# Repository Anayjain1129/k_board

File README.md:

# K-Board

# Features:

- Rotary Encoder for volume control
- Raspberry Pi Pico
- Customised layout
- QMK firmware
- Awesome Case

# Schematics

# PCB

# Case

# 3d View of all parts together

# BOM
| Name | Quantity | Cost | Link |
|------|----------|------|------|
| TTC Silent Red V3 | 84 | $45.11 | [Buy](https://stackskb.com/store/ttc-silent-red-v3-switch/) |
| Durock Smokey Screw-In Stabilizers V2 (4+1 w/ 6.25u spacebar) | 1 | $17.01 | [Buy](https://stackskb.com/store/durock-smokey-screw-in-stabilizers-v2/) |
| EC11 Rotary Encoder with Switch | 1 | $0.00 | Self-sourced |
| Mount Fuji Premium Moa Profile PBT Keycap | 1 | $28.78 | [Buy](https://curiositycaps.in/products/fugaju-premium-moa-profile-pbt-keycap?_pos=21&_sid=c0043ab41&_ss=r) |
| Diode 1N4148 Through-Hole | 100 | $1.06 | [Buy](https://www.amazon.in/dp/B084ZP5BJ3) |
| PCB - (Black Color) | 5 | $40.00 | [Buy](https://jlcpcb.com/) |
| Raspberry Pi Pico | 1 | $6.40 | [Buy](https://www.amazon.in/Raspberry-Pi-Headers-Soldered-Micro/dp/B08WPNM7JB) |
| Heatset and Screws | 1 | $0.00 | Self-sourced |
| Case (top, mid, bot) | 1 | $0.00 | Self-sourced |
| **Total** | | **$138.36** | |

The price may fluctuate due to dollar market trend

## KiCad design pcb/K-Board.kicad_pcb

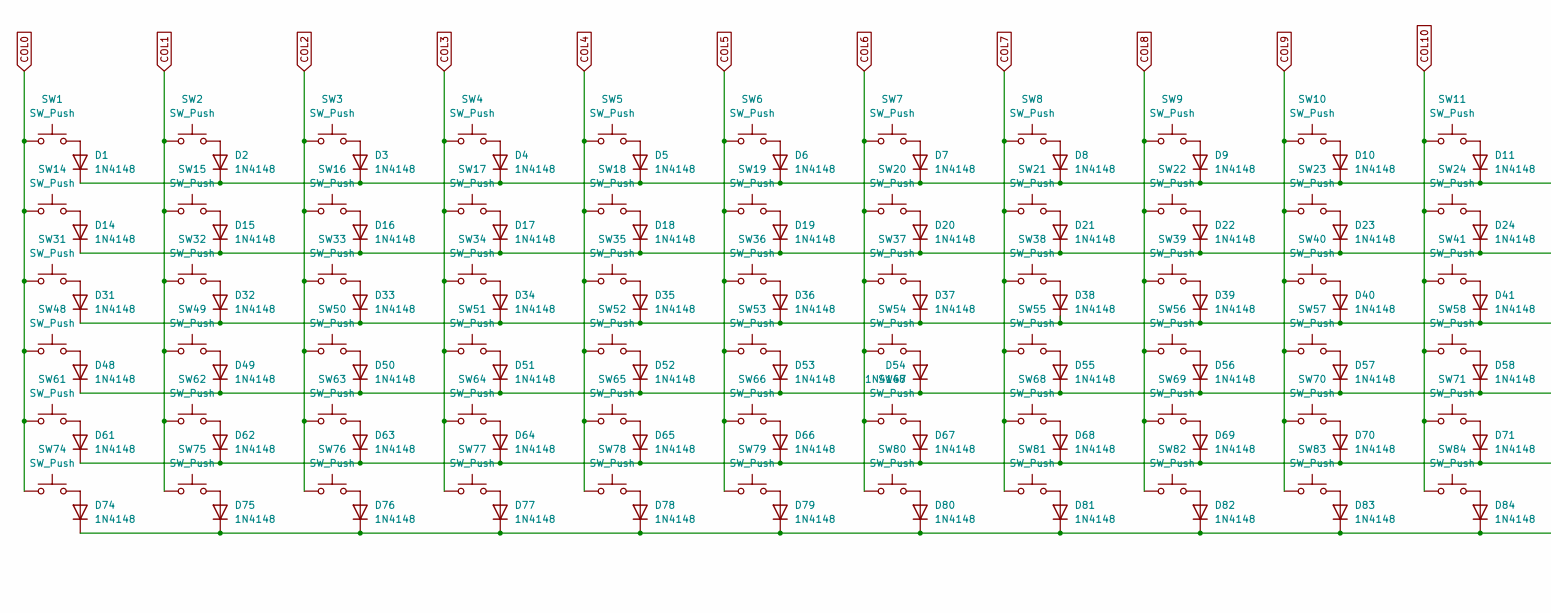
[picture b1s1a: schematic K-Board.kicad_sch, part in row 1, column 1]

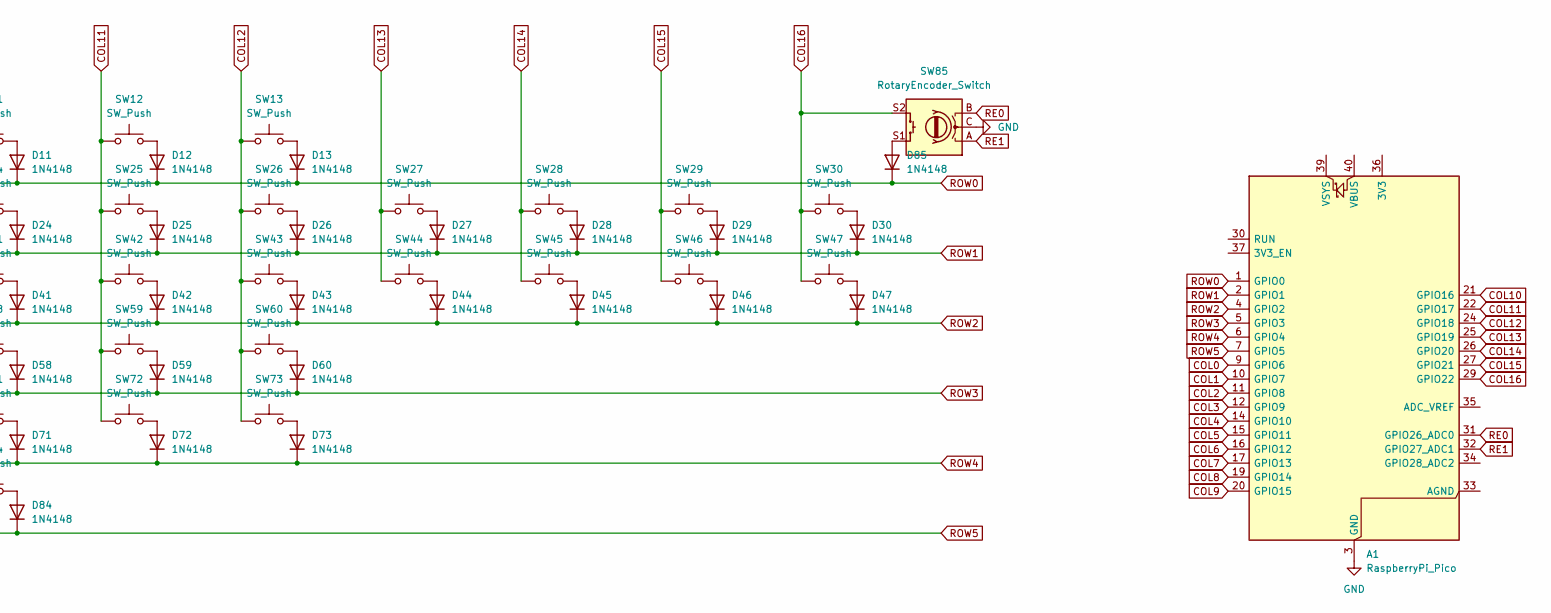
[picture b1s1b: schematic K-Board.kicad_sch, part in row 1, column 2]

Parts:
A1: RaspberryPi_Pico; RaspberryPi_Pico_Common_Unspecified
D1, D2, D3, D4, D5, D6, D7, D8, D9, D10, D11, D12, D13, D14, D15, D16, D17, D18, D19, D20, D21, D22, D23, D24, D25, D26, D27, D28, D29, D30, D31, D32, D33, D34, D35, D36, D37, D38, D39, D40, D41, D42, D43, D44, D45, D46, D47, D48, D49, D50, D51, D52, D53, D54, D55, D56, D57, D58, D59, D60, D61, D62, D63, D64, D65, D66, D67, D68, D69, D70, D71, D72, D73, D74, D75, D76, D77, D78, D79, D80, D81, D82, D83, D84, D85: 1N4148; D_DO-35_SOD27_P7.62mm_Horizontal
SW1, SW2, SW3, SW4, SW5, SW6, SW7, SW8, SW9, SW10, SW11, SW12, SW13, SW14, SW15, SW16, SW17, SW18, SW19, SW20, SW21, SW22, SW23, SW24, SW25, SW26, SW27, SW28, SW29, SW31, SW33, SW34, SW35, SW36, SW37, SW38, SW39, SW40, SW41, SW42, SW43, SW44, SW46, SW48, SW49, SW50, SW51, SW52, SW53, SW54, SW55, SW56, SW57, SW58, SW60, SW62, SW63, SW64, SW65, SW66, SW67, SW68, SW69, SW70, SW71, SW73, SW74, SW79, SW80, SW81, SW82, SW83, SW84: SW_Push; SW_Cherry_MX_1.00u_PCB
SW30: SW_Push; SW_Cherry_MX_2.00u_PCB
SW32, SW45: SW_Push; SW_Cherry_MX_1.50u_PCB
SW47, SW72: SW_Push; SW_Cherry_MX_1.75u_PCB
SW59, SW61: SW_Push; SW_Cherry_MX_2.25u_PCB
SW75, SW76, SW77: SW_Push; SW_Cherry_MX_1.25u_PCB
SW78: SW_Push; SW_Cherry_MX_6.25u_PCB
SW85: RotaryEncoder_Switch; RotaryEncoder_Alps_EC12E-Switch_Vertical_H20mm_CircularMoun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

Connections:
COL0: A1.9 (GPIO6), SW1.1, SW14.1, SW31.1, SW48.1, SW61.1, SW74.1
COL1: A1.10 (GPIO7), SW2.1, SW15.1, SW32.1, SW49.1, SW62.1, SW75.1
COL2: A1.11 (GPIO8), SW3.1, SW16.1, SW33.1, SW50.1, SW63.1, SW76.1
COL3: A1.12 (GPIO9), SW4.1, SW17.1, SW34.1, SW51.1, SW64.1, SW77.1
COL4: A1.14 (GPIO10), SW5.1, SW18.1, SW35.1, SW52.1, SW65.1, SW78.1
COL5: A1.15 (GPIO11), SW6.1, SW19.1, SW36.1, SW53.1, SW66.1, SW79.1
COL6: A1.16 (GPIO12), SW7.1, SW20.1, SW37.1, SW54.1, SW67.1, SW80.1
COL7: A1.17 (GPIO13), SW8.1, SW21.1, SW38.1, SW55.1, SW68.1, SW81.1
COL8: A1.19 (GPIO14), SW9.1, SW22.1, SW39.1, SW56.1, SW69.1, SW82.1
COL9: A1.20 (GPIO15), SW10.1, SW23.1, SW40.1, SW57.1, SW70.1, SW83.1
COL10: A1.21 (GPIO16), SW11.1, SW24.1, SW41.1, SW58.1, SW71.1, SW84.1
COL11: A1.22 (GPIO17), SW12.1, SW25.1, SW42.1, SW59.1, SW72.1
COL12: A1.24 (GPIO18), SW13.1, SW26.1, SW43.1, SW60.1, SW73.1
COL13: A1.25 (GPIO19), SW27.1, SW44.1
COL14: A1.26 (GPIO20), SW28.1, SW45.1
COL15: A1.27 (GPIO21), SW29.1, SW46.1
COL16: A1.29 (GPIO22), SW30.1, SW47.1, SW85.S2
GND: A1.3 (GND), A1.8 (GND), A1.13 (GND), A1.18 (GND), A1.23 (GND), A1.28 (GND), A1.38 (GND), SW85.C
unnamed: D1.2 (A), SW1.2
unnamed: D2.2 (A), SW2.2
unnamed: D3.2 (A), SW3.2
unnamed: D4.2 (A), SW4.2
unnamed: D5.2 (A), SW5.2
unnamed: D6.2 (A), SW6.2
unnamed: D7.2 (A), SW7.2
unnamed: D8.2 (A), SW8.2
unnamed: D9.2 (A), SW9.2
unnamed: D10.2 (A), SW10.2
unnamed: D11.2 (A), SW11.2
unnamed: D12.2 (A), SW12.2
unnamed: D13.2 (A), SW13.2
unnamed: D14.2 (A), SW14.2
unnamed: D15.2 (A), SW15.2
unnamed: D16.2 (A), SW16.2
unnamed: D17.2 (A), SW17.2
unnamed: D18.2 (A), SW18.2
unnamed: D19.2 (A), SW19.2
unnamed: D20.2 (A), SW20.2
unnamed: D21.2 (A), SW21.2
unnamed: D22.2 (A), SW22.2
unnamed: D23.2 (A), SW23.2
unnamed: D24.2 (A), SW24.2
unnamed: D25.2 (A), SW25.2
unnamed: D26.2 (A), SW26.2
unnamed: D27.2 (A), SW27.2
unnamed: D28.2 (A), SW28.2
unnamed: D29.2 (A), SW29.2
unnamed: D30.2 (A), SW30.2
unnamed: D31.2 (A), SW31.2
unnamed: D32.2 (A), SW32.2
unnamed: D33.2 (A), SW33.2
unnamed: D34.2 (A), SW34.2
unnamed: D35.2 (A), SW35.2
unnamed: D36.2 (A), SW36.2
unnamed: D37.2 (A), SW37.2
unnamed: D38.2 (A), SW38.2
unnamed: D39.2 (A), SW39.2
unnamed: D40.2 (A), SW40.2
unnamed: D41.2 (A), SW41.2
unnamed: D42.2 (A), SW42.2
unnamed: D43.2 (A), SW43.2
unnamed: D44.2 (A), SW44.2
unnamed: D45.2 (A), SW45.2
unnamed: D46.2 (A), SW46.2
unnamed: D47.2 (A), SW47.2
unnamed: D48.2 (A), SW48.2
unnamed: D49.2 (A), SW49.2
unnamed: D50.2 (A), SW50.2
unnamed: D51.2 (A), SW51.2
unnamed: D52.2 (A), SW52.2
unnamed: D53.2 (A), SW53.2
unnamed: D54.2 (A), SW54.2
unnamed: D55.2 (A), SW55.2
unnamed: D56.2 (A), SW56.2
unnamed: D57.2 (A), SW57.2
unnamed: D58.2 (A), SW58.2
unnamed: D59.2 (A), SW59.2
unnamed: D60.2 (A), SW60.2
unnamed: D61.2 (A), SW61.2
unnamed: D62.2 (A), SW62.2
unnamed: D63.2 (A), SW63.2
unnamed: D64.2 (A), SW64.2
unnamed: D65.2 (A), SW65.2
unnamed: D66.2 (A), SW66.2
unnamed: D67.2 (A), SW67.2
unnamed: D68.2 (A), SW68.2
unnamed: D69.2 (A), SW69.2
unnamed: D70.2 (A), SW70.2
unnamed: D71.2 (A), SW71.2
unnamed: D72.2 (A), SW72.2
unnamed: D73.2 (A), SW73.2
unnamed: D74.2 (A), SW74.2
unnamed: D75.2 (A), SW75.2
unnamed: D76.2 (A), SW76.2
unnamed: D77.2 (A), SW77.2
unnamed: D78.2 (A), SW78.2
unnamed: D79.2 (A), SW79.2
unnamed: D80.2 (A), SW80.2
unnamed: D81.2 (A), SW81.2
unnamed: D82.2 (A), SW82.2
unnamed: D83.2 (A), SW83.2
unnamed: D84.2 (A), SW84.2
unnamed: D85.2 (A), SW85.S1
RE0: A1.31 (GPIO26_ADC0), SW85.B
RE1: A1.32 (GPIO27_ADC1), SW85.A
ROW0: A1.1 (GPIO0), D1.1 (K), D2.1 (K), D3.1 (K), D4.1 (K), D5.1 (K), D6.1 (K), D7.1 (K), D8.1 (K), D9.1 (K), D10.1 (K), D11.1 (K), D12.1 (K), D13.1 (K), D85.1 (K)
ROW1: A1.2 (GPIO1), D14.1 (K), D15.1 (K), D16.1 (K), D17.1 (K), D18.1 (K), D19.1 (K), D20.1 (K), D21.1 (K), D22.1 (K), D23.1 (K), D24.1 (K), D25.1 (K), D26.1 (K), D27.1 (K), D28.1 (K), D29.1 (K), D30.1 (K)
ROW2: A1.4 (GPIO2), D31.1 (K), D32.1 (K), D33.1 (K), D34.1 (K), D35.1 (K), D36.1 (K), D37.1 (K), D38.1 (K), D39.1 (K), D40.1 (K), D41.1 (K), D42.1 (K), D43.1 (K), D44.1 (K), D45.1 (K), D46.1 (K), D47.1 (K)
ROW3: A1.5 (GPIO3), D48.1 (K), D49.1 (K), D50.1 (K), D51.1 (K), D52.1 (K), D53.1 (K), D54.1 (K), D55.1 (K), D56.1 (K), D57.1 (K), D58.1 (K), D59.1 (K), D60.1 (K)
ROW4: A1.6 (GPIO4), D61.1 (K), D62.1 (K), D63.1 (K), D64.1 (K), D65.1 (K), D66.1 (K), D67.1 (K), D68.1 (K), D69.1 (K), D70.1 (K), D71.1 (K), D72.1 (K), D73.1 (K)
ROW5: A1.7 (GPIO5), D74.1 (K), D75.1 (K), D76.1 (K), D77.1 (K), D78.1 (K), D79.1 (K), D80.1 (K), D81.1 (K), D82.1 (K), D83.1 (K), D84.1 (K)

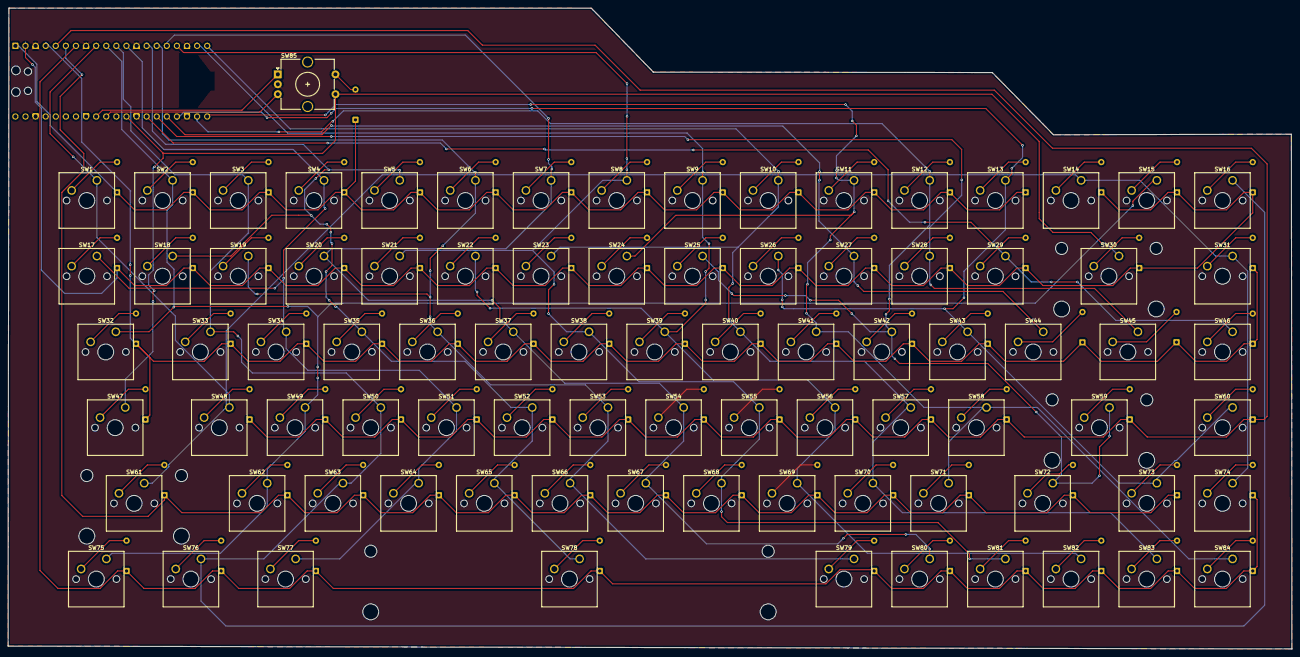
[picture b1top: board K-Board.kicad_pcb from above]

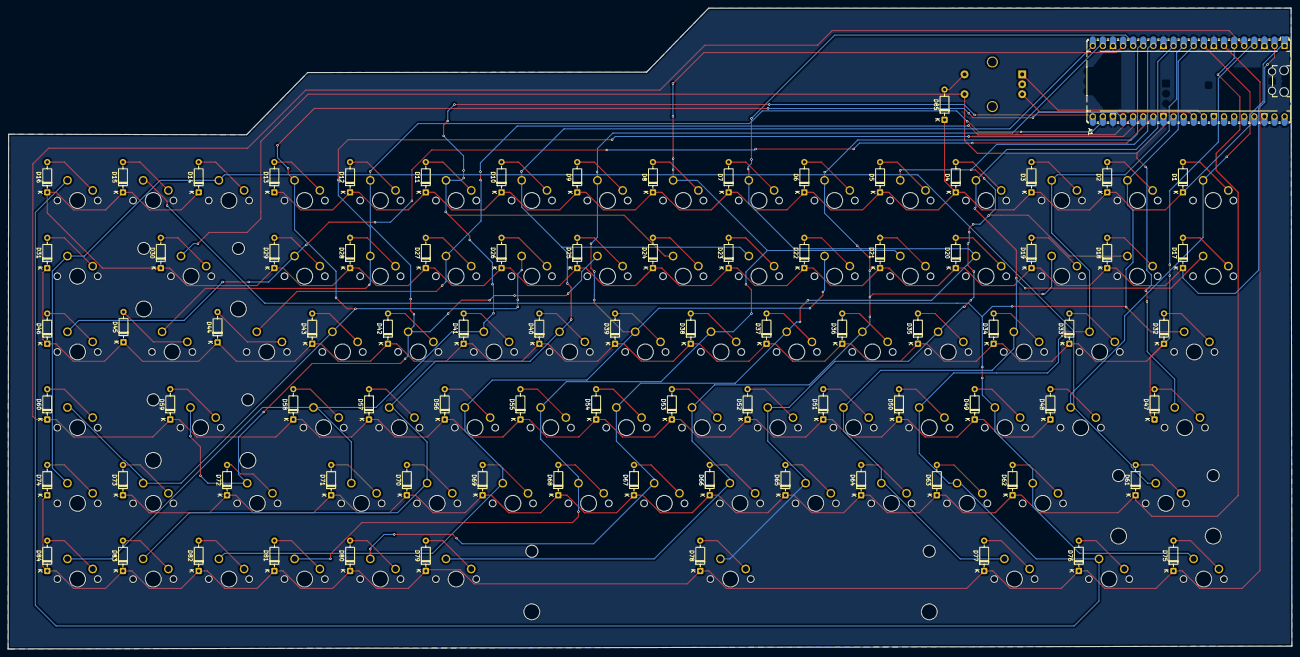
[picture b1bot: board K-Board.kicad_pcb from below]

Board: 2 copper layers, 323.1 x 161.3 mm, 171 parts (86 on the bottom side), 111 nets.

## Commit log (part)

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2026-05-02 1st journal
    Documented the initial brainstorming and schematic design for a custom keyboard project, including a time lapse link and an image.
2026-05-02 Edit journal entry for May 3rd
    Removed brackets and corrected minor typos in the journal entry.
2026-05-07 Update journal with May 7th entry
    Document progress on schematics and PCB design.
2026-05-09 Update journal with May 10th PCB completion entry
    Documented completion of PCB wiring and design details.
2026-05-10 Update journal with PCB and switch model progress
    Added details about 3D models of switches and PCB rendering.
2026-05-11 Update journal with May 11th progress
    Document progress on keyboard case design and time spent learning KiCad.
2026-05-12 Update journal with May 12th entry
    Added new entry for May 12th detailing work on case and ideas.
2026-05-13 Add May 13th journal entry
    Added journal entry for May 13th detailing screw hole creation.
2026-05-16 Update journal with May 16th entry on keyboard project
    Document progress on cyberpunk themed keyboard project, including design brainstorming and time spent.
2026-05-19 Document progress on case design for May 19th
    Added a new entry for May 19th detailing progress on the case design and included screenshots.
